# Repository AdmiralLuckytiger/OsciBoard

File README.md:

# __OsciBoard__: Wein Bridge Oscillator

## 👋 Welcome

This repository walks you through the design, build, and testing process of a Wien Bridge Oscillator.

Inside, you'll find the steps we followed to bring the project to life, along with additional thoughts and notes added along the way. Since this has been an iterative process, we’ve included reflections and improvements made throughout the journey.

## 🎯 Objective

The goal of this project is to design and implement a sinusoidal oscillator operating at 10 kHz. To achieve this, we’ve chosen a classic Wien Bridge Oscillator as our base circuit. From there, the signal will be enhanced using a variable gain stage to improve performance and stability.

To analyze the oscillator’s output, we’ll be using a digital system. This means the signal needs to be conditioned and digitized before processing. For digitization, we'll use the ADC (Analog-to-Digital Converter) integrated in a System on Chip (SoC). This SoC includes:

- A programmable logic section (FPGA)

- Two microprocessors

Because of this setup, the oscillator's output voltage must remain within the 0 to 3.3V range to be safely read by the ADC. Protective measures will also be implemented to prevent any out-of-range voltages.

Once the signal is digitized, we aim to measure two key parameters:

- The frequency of the oscillation

- The amplitude of the waveform

The frequency value will be displayed on a 7-segment display connected via a shield to the development board.

## 🧪 Simulations
In this section, we describe the proposed system in more detail—breaking down the main stages and showing how we simulated each part. 

### 💡 Solution Overview
> [!IMPORTANT]
> We're required to use a Wien Bridge Oscillator as a constraint of this project.
> Fortunately, this type of oscillator is a great fit for our goals—it’s inexpensive, well-suited for our frequency range, and has a smooth startup behavior.

Our solution is built around a Wien Bridge Oscillator with adjustable gain. The oscillator generates a sinusoidal signal that is sent to two separate subcircuits:

---

### 🔎 Subcircuit 1: Frequency Measurement Path

This branch of the circuit is responsible for preparing the signal so that its frequency can be measured digitally: 

- First, a summing amplifier introduces an offset and scales the signal.

- Then, an inverting amplifier corrects the polarity, resulting in a signal fully within the positive range.

Together, these stages ensure the signal is properly conditioned for reliable digital processing.

---

### 🔎 Subcircuit 2: Amplitude Measurament Path

This second branch is dedicated to measuring the amplitude of the oscillation: 

- A precision full-wave rectifier caaptures the full waveform.

- This is followed by a two-pole low-pass filter, which smooths the signal to provide a stable DC value that reflects the original amplitude.

> [!WARNING]
> In this kind of project, where we're working with signals that carry important information, it's essential to use precision rectifiers—other types can significantly alter the signal. 

The solution we chose is based on generating two separate signals—one for measuring amplitude and the other for frequency. While this approach was selected somewhat arbitrarily, it gives us a great opportunity to implement and experiment with different circuits along the way.

> [!CAUTION]
> We could have gone with a normalized filter, like a Chebyshev filter. However, since we're not working in a restrictive environment and the only key requirement is unity gain, we chose this particular design. In the lab, other topologies ran into some issues with maintaining the correct gain. That said, future improvements could definitely benefit from using normalized filters for better performance.

### 🖥️ Simulation Enviorament 

The entire system was simulated using LTSpice, a tool provided for free by Analog Devices. We chose LTSpice as our main simulation environment because it's free and includes most of the component models we’re using out of the box.

> [!NOTE]
> The component values used in the simulation were selected through a combination of theoretical calculations and manual tuning. The theory we applied comes from "Fundamentals of Electronics: Oscillators and Advanced Electronics Topics."

### 🧾 Results

We identified three critical signals in the system:

- The output of the Wien Bridge Oscillator
- The frequency output signal
- The amplitude output signal

The simulation results for these signals are consistent with theoretical expectations.

> [!NOTE]
> Beyond these main signals, the simulation also provided valuable insights through intermediary signals. These will be especially helpful when debugging the real-world circuit.

## 👨‍🔬 Lab Tests
Once the simulation was completed and validated according to the project specifications, we moved on to testing the core building blocks of our system. A full system test would have required significantly more time and resources, and the errors we could catch with a complete system weren’t considered critical. 

> [!NOTE]
> In our first approach, we focused only on testing the Wien Bridge Oscillator. However, this decision led us to miss some issues in the full-wave precision rectifier block before sending the schematics out for fabrication. That ended up being a mistake and taught us a valuable lesson—future projects should definitely include testing of all critical blocks early on.

### ✅ Wein Bridge Oscillator

Without the variable gain circuit, the oscillator output was saturated and had no amplitude control, which made it unusable in its initial form.

### ✅ Full Wave Precission Rectifier

> [!NOTE]
> Our first version of this block used standard diodes, which introduced distortion into the signal. We solved this issue by switching to Schottky diodes with a fast recovery time, which worked much better in this case.

## ▶️ PCB Design
This step was developed in parallel with the lab testing phase. We chose KiCad 8 for the PCB design because it’s a user-friendly tool that fits well with the scope of our project.

> [!NOTE]
> While KiCad’s documentation is excellent, we also used the book "Design an RP2040 Board with KiCad" as our primary guide throughout the design process.
---
### ✅ Schematics
We translated the schematics from our simulation into KiCad's tool. This step also gave us the opportunity to:

- Annotate key design aspects
- Select the appropriate component footprints, which helped with our component selection
- Approach the project more formally

---
### ✅ Layout
The PCB layout is just as important as the schematics. For this part, we took an iterative approach, making small improvements and corrections with each step.

We added as many debug pins as possible to improve the system's observability. 

> [!CAUTION]
> A mistake worth highlighting is our use of non-standard debug pins. This could potentially cause short circuits when measuring with oscilloscope probes. In future designs, we’ll use standard debug pin layouts to make debugging easier and safer. 

> [!NOTE]
> Before starting the layout, it’s important to consider the manufacturer’s capabilities. Certain design parameters, such as trace width or via size, may be limited by the manufacturer, so it's a good idea to choose them early in the process.

We also made use of flooded zones, which helped with power pin connections and provided some shielding for noise-sensitive components.

> [!NOTE]
> In future designs, we plan to avoid placing vias on the component pads, as it negatively affects the quality of solder connections.
---
### ✅ Components Selection
Since we’re hand-soldering the components ourselves, we limited our selection to standardized 1206 and 0805 footprints, which are easier to solder manually. 

> [!IMPORTANT]
> When working with circuits where component values are critical, we recommend testing a range of values. Despite validating component values on a breadboard, one of our resistors had a tolerance issue in the final PCB version, which caused the Wien Bridge Oscillator to fail. This issue wasn’t caught until after over eight hours of debugging—a painful lesson that we hope to avoid in future projects. 
---
#### 💰 Purchase
For simplicity, we sourced all our components from a single electronics shop.

> [!NOTE]
> Before making any purchases, make sure the shop handles taxes. It can save you from unexpected costs down the road. 

## 🎉 Results
In the following images, you can see the board being tested. 

---

## 🧠 Digital Circuit Overview

A core component of this project is the development of a custom digital circuit deployed on the PYNQ-Z2 development board. This circuit is responsible for measuring and displaying the frequency of an input signal. It operates synchronously using the board’s external 125 MHz clock source.

### ⚙️ Core Functional Blocks

- **XADC**  
  The Xilinx Analog-to-Digital Converter (XADC) is used to sample the analog input signal. The IP core is configured to operate at 1 MSPS (Mega Samples Per Second), which provides sufficient resolution to support the frequency measurement system.

- **Frequency Counter**  
  A dedicated module counts the number of signal transitions (edges) within a fixed time window of 0.1 seconds. This interval allows us to display the frequency in kilohertz (kHz) with two decimal places of precision.

- **Binary to Binary-Coded Decimal (BCD) Converter**  
  To prepare the computed frequency value for display, a binary-to-BCD converter is implemented using the Double Dabble algorithm. This conversion is necessary for driving human-readable outputs like 7-segment displays.

- **Display Interface**  
  The BCD-encoded frequency value is passed to a display driver that outputs it via 7-segment displays, allowing for visualization of the measured frequency.

---

### 📊 Simulation Results

Below are visual results from the simulations of each key subcircuit in the system. These illustrate the signal's journey from digitization to binary-coded decimal (BCD) conversion.

#### 🔍 XADC (Analog-to-Digital Conversion)

This image shows the output of the XADC operating at 1 MSPS with 100 samples per point. It represents the digitized version of the input analog signal.

#### 📟 Frequency Counter

These simulations depict the frequency counter circuit in action. The first image shows the primary frequency counting logic, while the second provides a complementary perspective of the counter’s operation.

#### 🔢 Binary to BCD Conversion

Finally, the image below demonstrates the output of the binary to BCD converter. This is the final step in the digital signal processing pipeline, converting the raw binary frequency value into a human-readable decimal format.

---

### 💡 Additional Notes

This system is entirely implemented in VHDL and synthesized using Xilinx Vivado. For detailed implementation instructions, configuration parameters, and deployment steps, refer to the [project documentation](./Prototype/Vivado/README.md).

---

## 🎉 Results 

The image below showcases our digital circuit in action, measuring the frequency of a sinusoidal signal generated by the Wien Bridge oscillator board.

In this setup, the Wien Bridge oscillator produces a stable sine wave, which is then processed by our digital circuit to determine its frequency.

As a final note, we would like to highlight the success of integrating both digital and analog circuitry in our project. This experience has provided us with invaluable insights into working across both domains, and has significantly increased our confidence in designing and implementing mixed-signal systems.

That said, throughout the development process, we also identified areas for improvement and noted several design mistakes that can be corrected in future iterations. These lessons will be crucial for refining our approach and achieving even better results in upcoming projects.

---

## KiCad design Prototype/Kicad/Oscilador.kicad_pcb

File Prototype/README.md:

### 📁 Project Files Overview

In this folder, you will find the primary prototype files created using **KiCad 8**. These files can be used to generate the necessary **Gerber files** required for PCB manufacturing.

Additionally, the folder includes:

* 💡 **Digital circuit design source files** – Schematics and layouts for the digital components of the project.
* 🧪 **Testbenches** – Simulation files used to verify the behavior and performance of individual subcircuits.

These resources collectively support both the hardware prototyping and digital logic development aspects of the project.

---

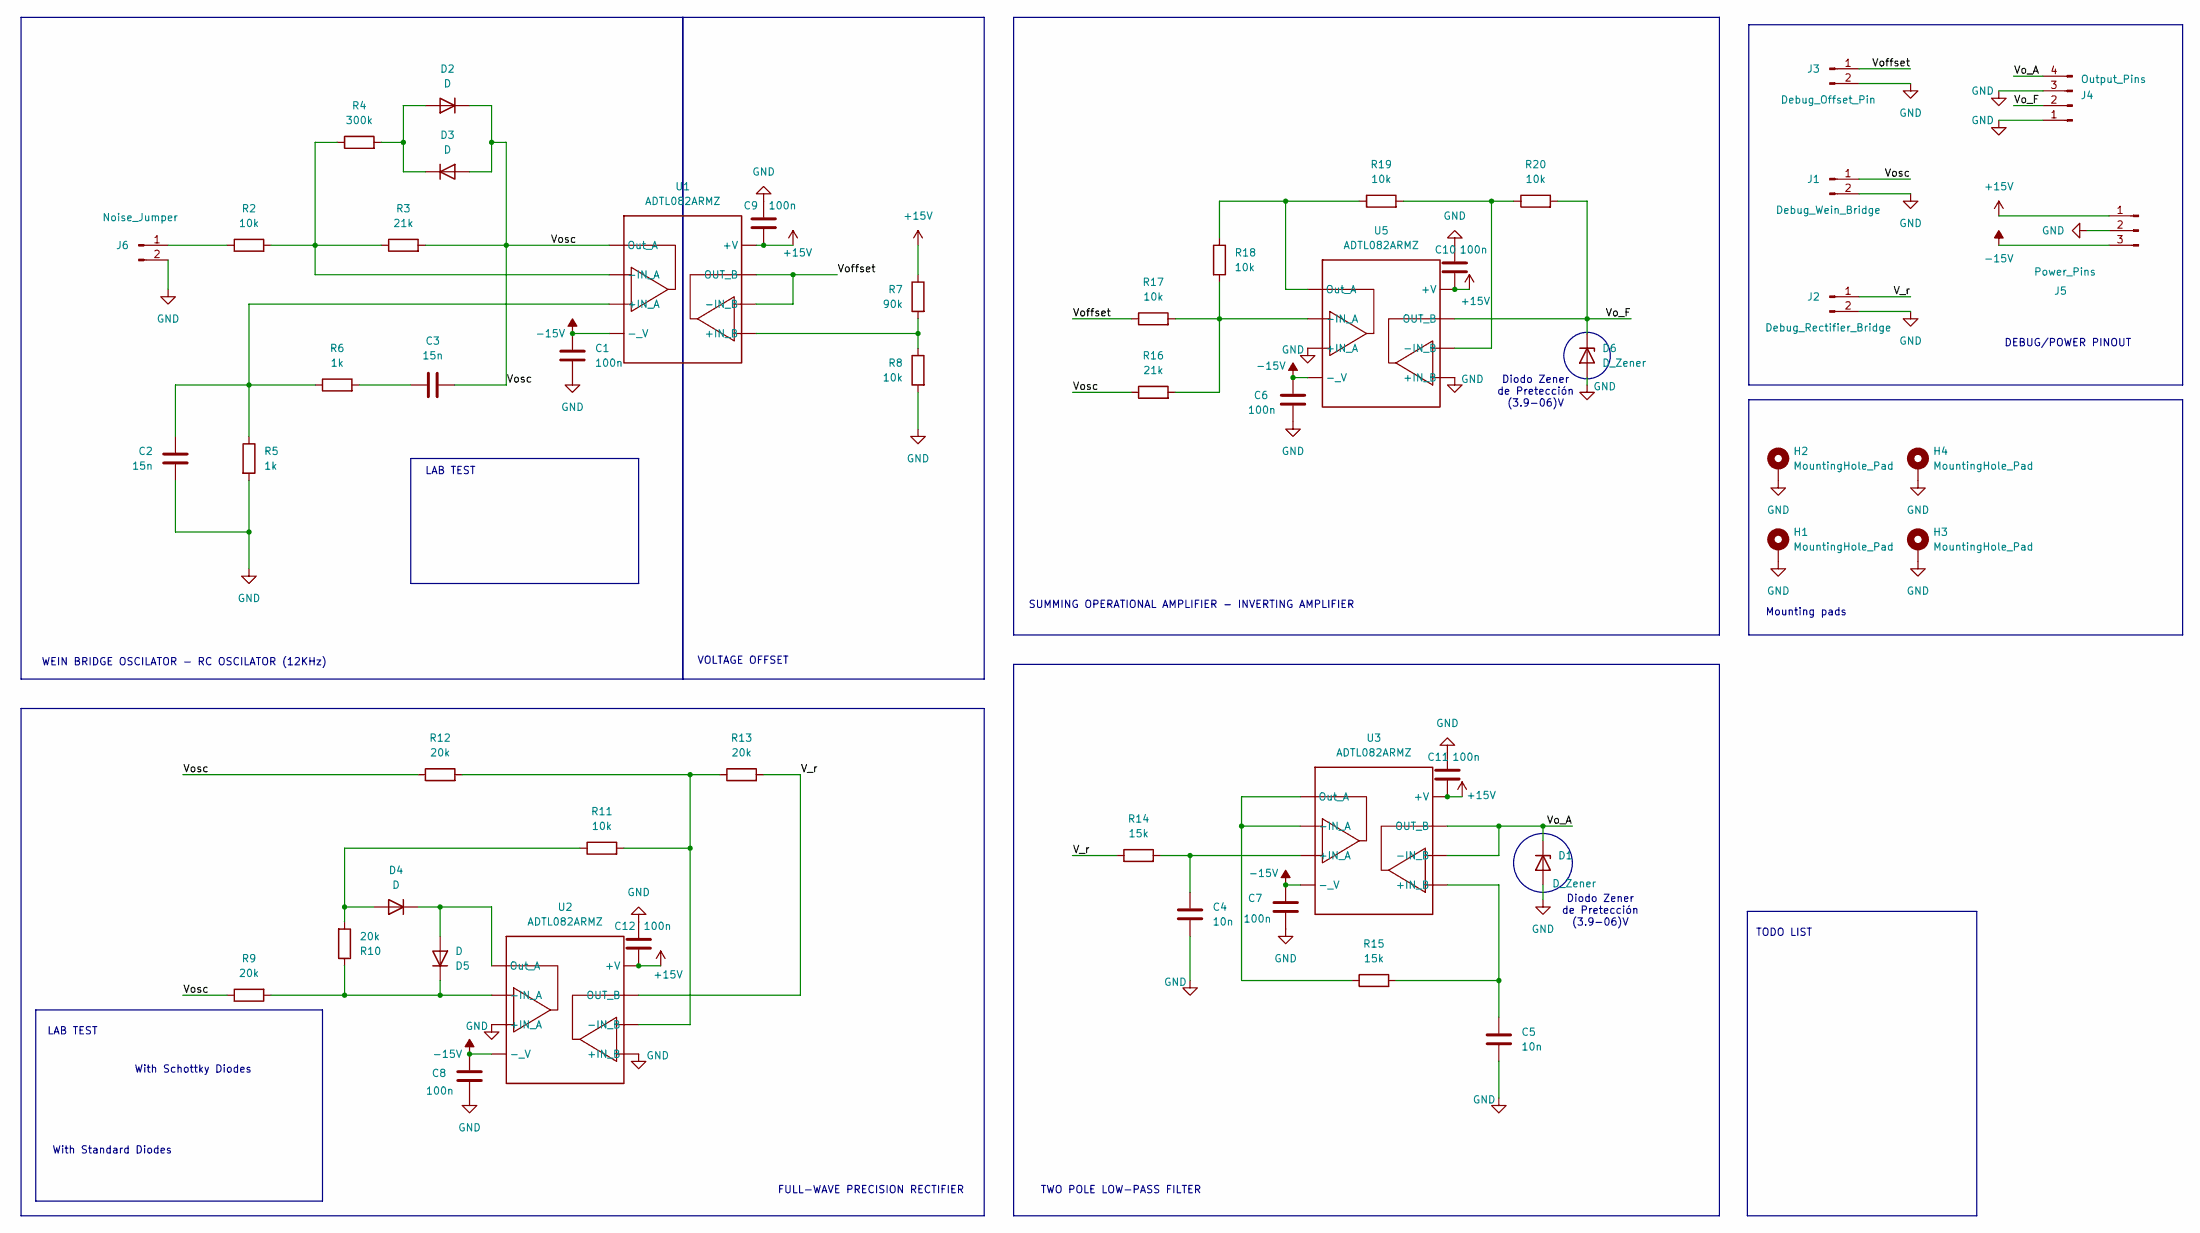
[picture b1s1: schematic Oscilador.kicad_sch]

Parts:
C1, C6, C7, C8, C9, C10, C11, C12: 100n; C_1206_3216Metric_Pad1.33x1.80mm_HandSolder
C2, C3: 15n; C_1206_3216Metric_Pad1.33x1.80mm_HandSolder
C4, C5: 10n; C_1206_3216Metric_Pad1.33x1.80mm_HandSolder
D1, D6: D_Zener; D_0805_2012Metric_Pad1.15x1.40mm_HandSolder
D2, D3, D4, D5: D; D_1206_3216Metric_Pad1.42x1.75mm_HandSolder
H1, H2, H3, H4: MountingHole_Pad; JLCPCB_Tooling_hole
J1: Debug_Wein_Bridge; PinHeader_1x02_P2.54mm_Vertical
J2: Debug_Rectifier_Bridge; PinHeader_1x02_P2.54mm_Vertical
J3: Debug_Offset_Pin; PinHeader_1x02_P2.54mm_Vertical
J4: Output_Pins; PinHeader_1x04_P2.54mm_Vertical
J5: Power_Pins; PinHeader_1x03_P2.54mm_Vertical
J6: Noise_Jumper; PinHeader_1x02_P2.54mm_Vertical
R2, R8, R11, R17, R18, R19, R20: 10k; R_1206_3216Metric_Pad1.30x1.75mm_HandSolder
R3, R16: 21k; R_1206_3216Metric_Pad1.30x1.75mm_HandSolder
R4: 300k; R_1206_3216Metric_Pad1.30x1.75mm_HandSolder
R5, R6: 1k; R_1206_3216Metric_Pad1.30x1.75mm_HandSolder
R7: 90k; R_1206_3216Metric_Pad1.30x1.75mm_HandSolder
R9, R10, R12, R13: 20k; R_1206_3216Metric_Pad1.30x1.75mm_HandSolder
R14, R15: 15k; R_1206_3216Metric_Pad1.30x1.75mm_HandSolder
U1, U2, U3, U5: ADTL082ARMZ; SOIC-8_3.9x4.9mm_P1.27mm

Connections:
+15V: C9.1, C10.1, C11.1, C12.1, J5.1, R7.1, U1.8 (+V), U2.8 (+V), U3.8 (+V), U5.8 (+V)
-15V: C1.2, C6.2, C7.2, C8.2, J5.3, U1.4 (-_V), U2.4 (-_V), U3.4 (-_V), U5.4 (-_V)
/V_r: J2.1, R13.2, R14.1, U2.7 (OUT_B)
/Vo_A: D1.1 (K), J4.4, U3.6 (-IN_B), U3.7 (OUT_B)
/Vo_F: D6.1 (K), J4.2, R20.2, U5.7 (OUT_B)
/Voffset: J3.1, R17.1, U1.6 (-IN_B), U1.7 (OUT_B)
/Vosc: C3.2, D2.1 (K), D3.2 (A), J1.1, R3.2, R9.1, R12.1, R16.1, U1.1 (Out_A)
GND: C1.1, C2.2, C4.2, C5.2, C6.1, C7.1, C8.1, C9.2, C10.2, C11.2, C12.2, D1.2 (A), D6.2 (A), H1.1, H2.1, H3.1, H4.1, J1.2, J2.2, J3.2, J4.1, J4.3, J5.2, J6.2, R5.2, R8.2, U2.3 (+IN_A), U2.5 (+IN_B), U5.3 (+IN_A), U5.5 (+IN_B)
unnamed: C3.1, R6.2
unnamed: D2.2 (A), D3.1 (K), R4.2
unnamed: D4.2 (A), R10.2, R11.1
unnamed: D4.1 (K), D5.2 (A), U2.1 (Out_A)
unnamed: D5.1 (K), R9.2, R10.1, U2.2 (-IN_A)
unnamed: J6.1, R2.1
unnamed: C2.1, R5.1, R6.1, U1.3 (+IN_A)
unnamed: R7.2, R8.1, U1.5 (+IN_B)
unnamed: R2.2, R3.1, R4.1, U1.2 (-IN_A)
unnamed: R11.2, R12.2, R13.1, U2.6 (-IN_B)
unnamed: C4.1, R14.2, U3.3 (+IN_A)
unnamed: C5.1, R15.2, U3.5 (+IN_B)
unnamed: R15.1, U3.1 (Out_A), U3.2 (-IN_A)
unnamed: R16.2, R17.2, R18.2, U5.2 (-IN_A)
unnamed: R19.2, R20.1, U5.6 (-IN_B)
unnamed: R18.1, R19.1, U5.1 (Out_A)

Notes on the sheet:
Mounting pads
Diodo Zener de Pretección (3.9-06)V
SUMMING OPERATIONAL AMPLIFIER - INVERTING AMPLIFIER
WEIN BRIDGE OSCILATOR - RC OSCILATOR (12KHz)
TODO LIST
With Schottky Diodes
With Standard Diodes
LAB TEST
FULL-WAVE PRECISION RECTIFIER
TWO POLE LOW-PASS FILTER
VOLTAGE OFFSET
DEBUG/POWER PINOUT

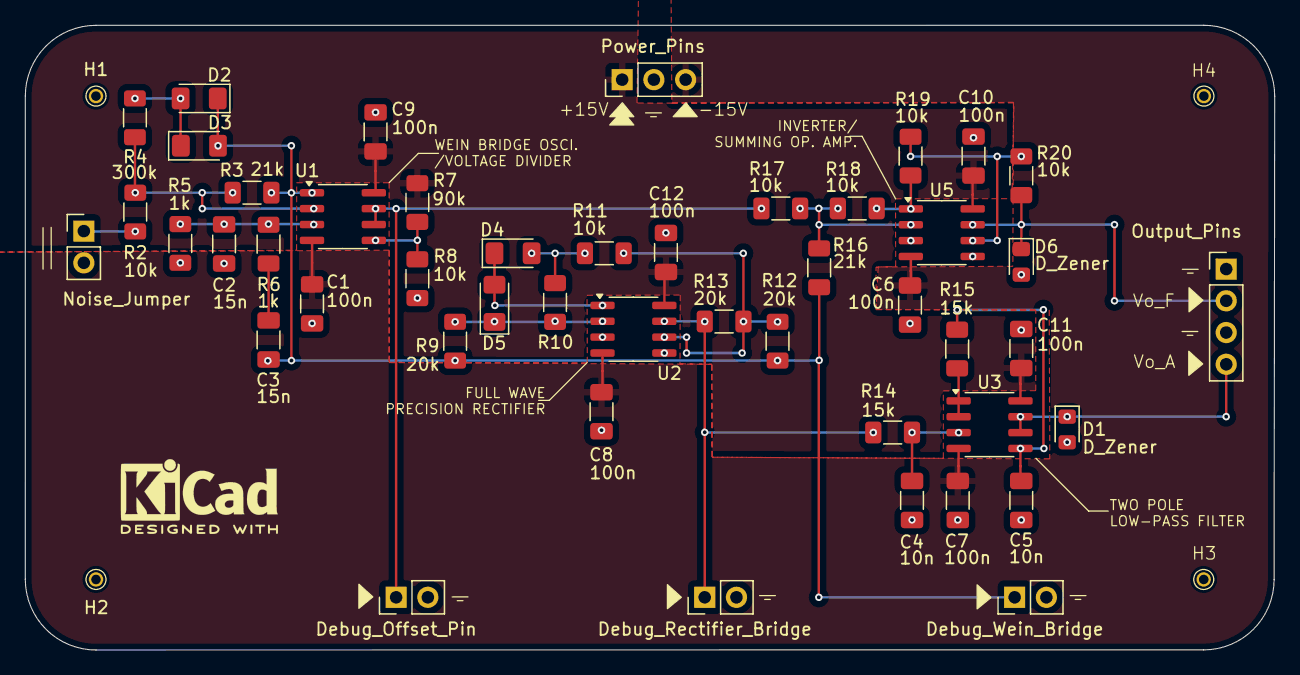
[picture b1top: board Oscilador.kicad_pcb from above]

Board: 2 copper layers, 100.0 x 50.0 mm, 51 parts (0 on the bottom side), 24 nets.

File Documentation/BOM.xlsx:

Reference | Value | Datasheet | Footprint | Qty | DNP | Description | enlace | Precio | Precio total |  | Pedido | Estado | revisión
C1,C6,C7,C8,C9,C10,C11,C12 | 100n | ~ | Capacitor_SMD:C_1206_3216Metric | 8 |  | Unpolarized capacitor | https://www.mouser.es/ProductDetail/Walsin/1206B104K500CT?qs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 | 0.11 | 0.88 | S | Sí | Entregado | si
C2,C3 | 15n | ~ | Capacitor_SMD:C_1206_3216Metric | 2 |  | Unpolarized capacitor | https://www.mouser.es/ProductDetail/Walsin/1206B153K250CT?qs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 | 0.13 | 0.26 | S | Sí | Entregado | si
C4,C5 | 10n | ~ | Capacitor_SMD:C_1206_3216Metric | 2 |  | Unpolarized capacitor | https://www.mouser.es/ProductDetail/Walsin/1206B103K631CT?qs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 | 0.11 | 0.22 | S | Sí | Entregado | si
D2,D3,D4,D5 | D | ~ | Diode_SMD:D_1206_3216Metric | 4 |  | Diode | https://www.mouser.es/ProductDetail/KYOCERA-AVX/SD1206S040S1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 | 0.33300000000000002 | 1.3320000000000001 | S | Sí | Entregado | si
J1 | Debug_Wein_Bridge | ~ | Connector_PinHeader_2.54mm:PinHeader_1x02_P2.54mm_Vertical | 1 |  | Generic connector, single row, 01x02, script generated |  |  | 0 |  |  | En Stock | si
J2 | Debug_Rectifier_Bridge | ~ | Connector_PinHeader_2.54mm:PinHeader_1x02_P2.54mm_Vertical | 1 |  | Generic connector, single row, 01x02, script generated |  |  | 0 |  |  | En Stock | si
J3 | Debug_Offset_Pin | ~ | Connector_PinHeader_2.54mm:PinHeader_1x02_P2.54mm_Vertical | 1 |  | Generic connector, single row, 01x02, script generated |  |  | 0 |  |  | En Stock | si
J4 | Output_Pins | ~ | Connector_PinHeader_2.54mm:PinHeader_1x04_P2.54mm_Vertical | 1 |  | Generic connector, single row, 01x04, script generated |  |  | 0 |  |  | En Stock | si
J5 | Power_Pins | ~ | Connector_PinHeader_2.54mm:PinHeader_1x03_P2.54mm_Vertical | 1 |  | Generic connector, single row, 01x03, script generated |  |  | 0 |  |  | En Stock | si
J6 | Noise_Jumper | ~ | Connector_PinHeader_2.54mm:PinHeader_1x02_P2.54mm_Vertical | 1 |  | Generic connector, single row, 01x02, script generated |  |  | 0 |  |  | En Stock | si
R2,R8,R11,R17,R18,R19,R20 | 10k | ~ | Resistor_SMD:R_1206_3216Metric | 7 |  | Resistor | https://www.mouser.es/ProductDetail/YAGEO/RT1206FRE0710KL?qs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 | 0.1 | 0.70000000000000007 | S | Sí | Entregado | si
R3,R16 | 21k | ~ | Resistor_SMD:R_1206_3216Metric | 2 |  | Resistor | https://www.mouser.es/ProductDetail/Bourns/CR1206-FX-2102ELF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 | 0.1 | 0.2 | S | Sí | Entregado | si, Modificada a 22KOhms
R4 | 300k | ~ | Resistor_SMD:R_1206_3216Metric | 1 |  | Resistor | https://www.mouser.es/ProductDetail/YAGEO/AC1206FR-07330KL?q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 | 0.1 | 0.1 | S | Sí | Entregado | si
R5,R6 | 1k | ~ | Resistor_SMD:R_1206_3216Metric | 2 |  | Resistor | https://www.mouser.es/ProductDetail/YAGEO/RC1206JR-071KP?qs=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 | 0.1 | 0.2 | S | Sí | Entregado | si
R7 | 90k | ~ | Resistor_SMD:R_1206_3216Metric | 1 |  | Resistor | https://www.mouser.es/ProductDetail/YAGEO/RT1206DRE0790KL?qs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 | 0.1 | 0.1 | S | Sí | Entregado | si
R9,R10,R12,R13 | 20k | ~ | Resistor_SMD:R_1206_3216Metric | 4 |  | Resistor | https://www.mouser.es/ProductDetail/YAGEO/RT1206FRD0720KL?qs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 | 0.1 | 0.4 | S | Sí | Entregado | si
R14,R15 | 15k | ~ | Resistor_SMD:R_1206_3216Metric | 2 |  | Resistor | https://www.mouser.es/ProductDetail/YAGEO/AF1206JR-0715KL?qs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 | 0.1 | 0.2 | S | Sí | Entregado | si
RV1,RV2 | R_Potentiometer | ~ | Potentiometer_SMD:Potentiometer_ACP_CA6-VSMD_Vertical | 2 |  | Potentiometer |  |  | 0 | X | - | -
U1,U2,U3,U5 | ADTL082ARMZ | https://www.mouser.co.uk/datasheet/2/609/ADTL082_084-1503470.pdf | Package_SO:SOIC-8_3.9x4.9mm_P1.27mm | 4 |  | Precision Amplifiers Industry Standard TL082 | https://www.mouser.es/ProductDetail/Analog-Devices/ADTL082AR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 | 2.2000000000000002 | 8.8000000000000007 | s | Sí | Entregado | si
D1,D6 | Diodo Zener |  | Diode_SMD:D_0805_2012Metric | 2 |  | Dido Zener | https://www.mouser.es/ProductDetail/Taiwan-Semiconductor/BZY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 | 0.3 | 0.6 | S | Sí | Entregado | si
 |  |  |  |  |  |  |  |  | 13.992000000000003

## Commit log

2025-03-21 Add basic structure of the proyect
2025-03-29 Improves readability of README
2025-03-29 Adds information about the BOM
2025-04-12 Add Logo to README file
2025-04-14 Improve readability of README
2025-04-14 Correct README
2025-04-24 Adds basic reasearch previous Hardware Design
2025-05-01 Adds designs of the digital circuit
2025-05-01 Expands documentation of the project
2025-05-01 Corrects some errors in README.md
2025-05-02 Update designs and testbenches
2025-05-02 Expands and correct README files
2025-05-02 Correct error README.md
2025-05-06 Update the sources and include constrains of the board
2025-05-06 Improve documentation
